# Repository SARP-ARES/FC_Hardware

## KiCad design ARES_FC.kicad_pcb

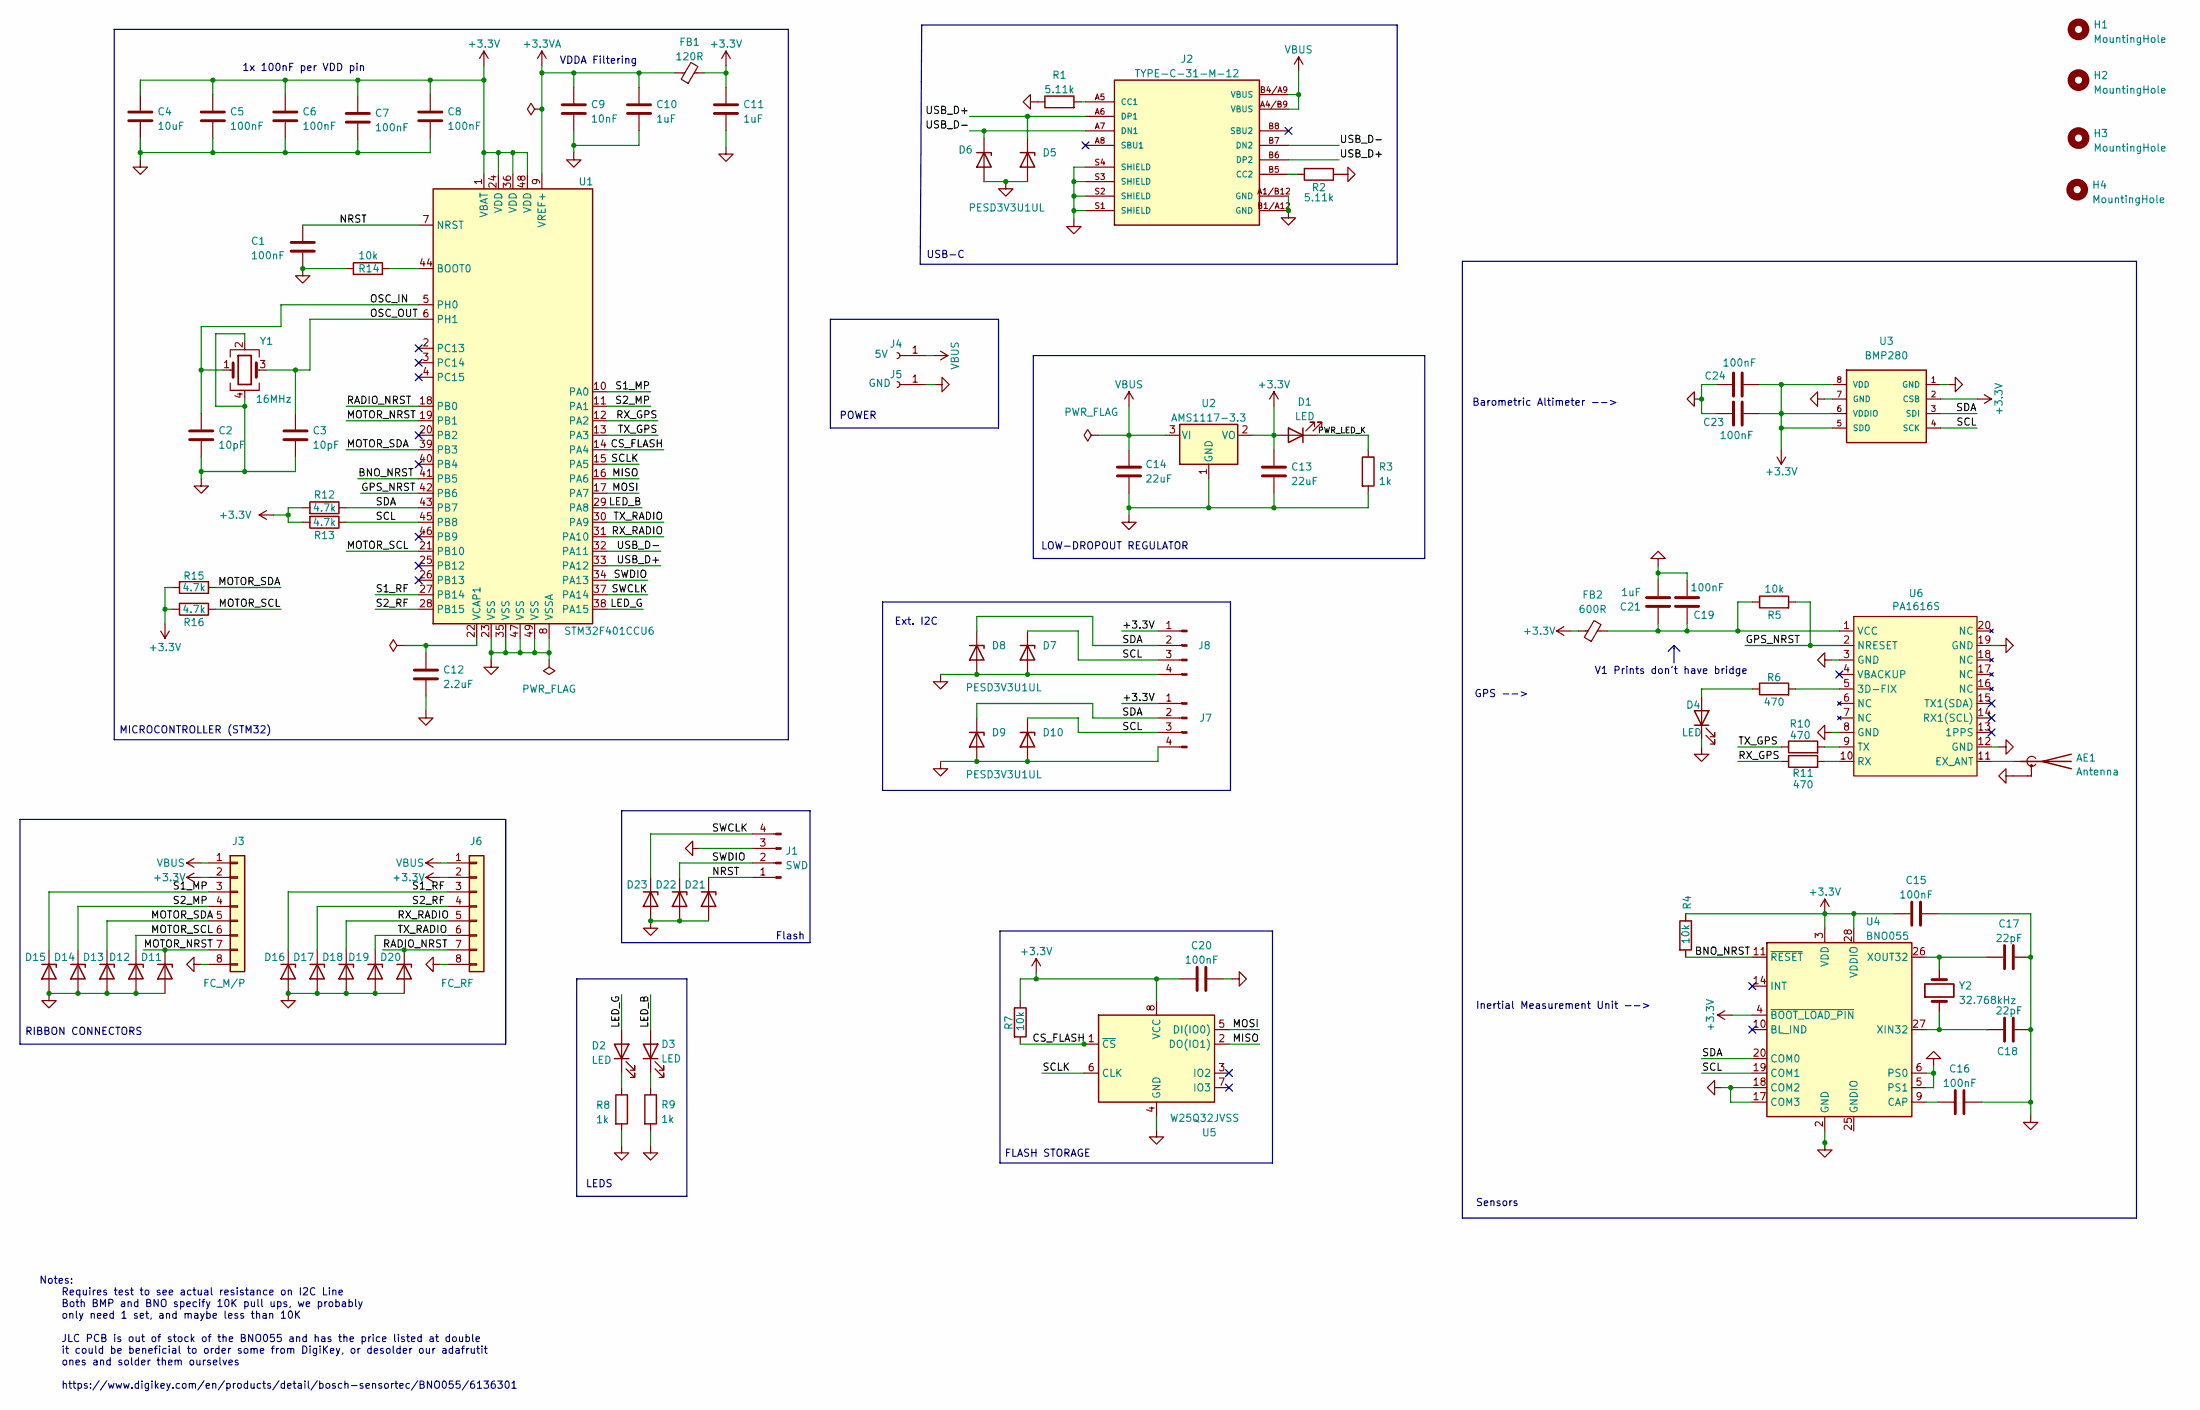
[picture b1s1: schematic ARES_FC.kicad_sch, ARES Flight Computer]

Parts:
AE1: Antenna; U.FL_Molex_MCRF_73412-0110_Vertical; LCSC Part C5137195
C1, C5, C6, C7, C8, C15, C16, C19, C20, C23, C24: 100nF; C_0402_1005Metric; LCSC Part C307331
C2, C3: 10pF; C_0402_1005Metric; LCSC Part C32949
C4: 10uF; C_0603_1608Metric; LCSC Part C19702
C9: 10nF; C_0402_1005Metric; LCSC Part C15195
C10, C11, C21: 1uF; C_0402_1005Metric; LCSC Part C52923
C12: 2.2uF; C_0402_1005Metric; LCSC Part C12530
C13, C14: 22uF; C_0805_2012Metric; LCSC Part C5674
C17, C18: 22pF; C_0402_1005Metric; LCSC Part C466226
D1, D2: LED; LED_0603_1608Metric; LCSC Part C12624
D3: LED; LED_0603_1608Metric; LCSC Part C2288
D4: LED; LED_0603_1608Metric; LCSC Part C2290
D5, D6, D7, D8, D9, D10, D11, D12, D13, D14, D15, D16, D17, D18, D19, D20, D21, D22, D23: PESD3V3U1UL; D_SOD-882
FB1: 120R; L_0603_1608Metric; LCSC Part C85831
FB2: 600R; L_0603_1608Metric; LCSC Part C88976
H1, H2, H3, H4: MountingHole; MountingHole_2.2mm_M2
J1: SWD; PinHeader_1x04_P2.54mm_Vertical; LCSC Part C3025061
J2: TYPE-C-31-M-12; HRO_TYPE-C-31-M-12; PARTREV 2020.12.08; LCSC Part C165948
J3: FC_M/P; Molex_200528-0080_1x08-1MP_P1.00mm_Horizontal; LCSC Part C132510
J4: 5V; TestPoint_THTPad_2.5x2.5mm_Drill1.2mm
J5: GND; TestPoint_THTPad_2.5x2.5mm_Drill1.2mm
J6: FC_RF; Molex_200528-0080_1x08-1MP_P1.00mm_Horizontal; LCSC Part C132510
J7, J8: Conn_01x04_Pin; JST_SH_BM04B-SRSS-TB_1x04-1MP_P1.00mm_Vertical; LCSC Part C160390
R1, R2: 5.11k; R_0402_1005Metric; LCSC Part C25906
R3, R8, R9: 1k; R_0402_1005Metric; LCSC Part C11702
R4, R5, R7, R14: 10k; R_0402_1005Metric; LCSC Part C60490
R6, R10, R11: 470; R_0402_1005Metric; LCSC Part 0402WGJ0471TCE
R12, R13, R15, R16: 4.7k; R_0402_1005Metric; LCSC Part C25900
U1: STM32F401CCU6; QFN-48-1EP_7x7mm_P0.5mm_EP5.6x5.6mm; LCSC Part C79861
U2: AMS1117-3.3; SOT-223-3_TabPin2; LCSC Part C6186
U3: BMP280; XDCR_BMP280; PART_REV 1.19; LCSC Part C83291
U4: BNO055; LGA-28_5.2x3.8mm_P0.5mm; LCSC Part C93216
U5: W25Q32JVSS; SOIC-8_5.23x5.23mm_P1.27mm; LCSC Part C82344
U6: PA1616S; XCVR_CD-PA1616D; LCSC Part C9900146965
Y1: 16MHz; Crystal_SMD_3225-4Pin_3.2x2.5mm; LCSC Part C13738
Y2: 32.768kHz; Crystal_SMD_3215-2Pin_3.2x1.5mm; LCSC Part C32346

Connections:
+3.3V: C4.1, C5.1, C6.1, C7.1, C8.1, C11.1, C13.1, C15.1, C20.1, C23.2, C24.2, D1.2 (A), FB1.2, FB2.1, J3.2, J6.2, J7.1, J8.1, R4.1, R7.1, R12.2, R13.2, R15.2, R16.2, U1.1 (VBAT), U1.24 (VDD), U1.36 (VDD), U1.48 (VDD), U2.2 (VO), U3.2 (CSB), U3.5 (SDO), U3.6 (VDDIO), U3.8 (VDD), U4.3 (VDD), U4.4 (~BOOT_LOAD_PIN), U4.28 (VDDIO), U5.8 (VCC)
+3.3VA: C9.1, C10.1, FB1.1, U1.9 (VREF+)
/BNO_NRST: R4.2, U1.41 (PB5), U4.11 (~RESET)
/CS_FLASH: R7.2, U1.14 (PA4), U5.1 (~CS)
/GPS_NRST: R5.2, U1.42 (PB6), U6.2 (NRESET)
/LED_B: D3.2 (A), U1.29 (PA8)
/LED_G: D2.2 (A), U1.38 (PA15)
/MISO: U1.16 (PA6), U5.2 (DO(IO1))
/MOSI: U1.17 (PA7), U5.5 (DI(IO0))
/MOTOR_NRST: D11.1 (K), J3.7, U1.19 (PB1)
/MOTOR_SCL: D12.1 (K), J3.6, R16.1, U1.21 (PB10)
/MOTOR_SDA: D13.1 (K), J3.5, R15.1, U1.39 (PB3)
/NRST: C1.2, D21.1 (K), J1.1, U1.7 (NRST)
/OSC_IN: C2.1, U1.5 (PH0), Y1.1
/OSC_OUT: C3.1, U1.6 (PH1), Y1.3
/PWR_LED_K: D1.1 (K), R3.1
/RADIO_NRST: D20.1 (K), J6.7, U1.18 (PB0)
/RX_GPS: R11.1, U1.12 (PA2)
/RX_RADIO: D18.1 (K), J6.5, U1.31 (PA10)
/S1_MP: D15.1 (K), J3.3, U1.10 (PA0)
/S1_RF: D16.1 (K), J6.3, U1.27 (PB14)
/S2_MP: D14.1 (K), J3.4, U1.11 (PA1)
/S2_RF: D17.1 (K), J6.4, U1.28 (PB15)
/SCL: D7.1 (K), D10.1 (K), J7.3, J8.3, R13.1, U1.45 (PB8), U3.4 (SCK), U4.19 (COM1)
/SCLK: U1.15 (PA5), U5.6 (CLK)
/SDA: D8.1 (K), D9.1 (K), J7.2, J8.2, R12.1, U1.43 (PB7), U3.3 (SDI), U4.20 (COM0)
/SWCLK: D23.1 (K), J1.4, U1.37 (PA14)
/SWDIO: D22.1 (K), J1.2, U1.34 (PA13)
/TX_GPS: R10.1, U1.13 (PA3)
/TX_RADIO: D19.1 (K), J6.6, U1.30 (PA9)
/USB_D+: D5.1 (K), J2.A6 (DP1), J2.B6 (DP2), U1.33 (PA12)
/USB_D-: D6.1 (K), J2.A7 (DN1), J2.B7 (DN2), U1.32 (PA11)
GND: AE1.2 (Shield), C1.1, C2.2, C3.2, C4.2, C5.2, C6.2, C7.2, C8.2, C9.2, C10.2, C11.2, C12.2, C13.2, C14.2, C15.2, C16.2, C17.2, C18.2, C19.2, C20.2, C21.2, C23.1, C24.1, D4.1 (K), D5.2 (A), D6.2 (A), D7.2 (A), D8.2 (A), D9.2 (A), D10.2 (A), D11.2 (A), D12.2 (A), D13.2 (A), D14.2 (A), D15.2 (A), D16.2 (A), D17.2 (A), D18.2 (A), D19.2 (A), D20.2 (A), D21.2 (A), D22.2 (A), D23.2 (A), J1.3, J2.A1/B12 (GND), J2.B1/A12 (GND), J2.S1 (SHIELD), J2.S2 (SHIELD), J2.S3 (SHIELD), J2.S4 (SHIELD), J3.8, J5.1, J6.8, J7.4, J8.4, R1.1, R2.1, R3.2, R8.2, R9.2, R14.1, U1.8 (VSSA), U1.23 (VSS), U1.35 (VSS), U1.47 (VSS), U1.49 (VSS), U2.1 (GND), U3.1 (GND), U3.7 (GND), U4.2 (GND), U4.5 (PS1), U4.6 (PS0), U4.17 (COM3), U4.18 (COM2), U5.4 (GND), U6.3 (GND), U6.8 (GND), U6.12 (GND), U6.19 (GND), Y1.2, Y1.4
unnamed: AE1.1 (A), U6.11 (EX_ANT)
unnamed: D2.1 (K), R8.1
unnamed: D3.1 (K), R9.1
unnamed: D4.2 (A), R6.1
unnamed: J2.A5 (CC1), R1.2
unnamed: J2.B5 (CC2), R2.2
unnamed: R14.2, U1.44 (BOOT0)
unnamed: C12.1, U1.22 (VCAP1)
unnamed: C16.1, U4.9 (CAP)
unnamed: U4.15 (GNDIO), U4.16 (GNDIO), U4.25 (GNDIO)
unnamed: C18.1, U4.27 (XIN32), Y2.1
unnamed: C17.1, U4.26 (XOUT32), Y2.2
unnamed: R6.2, U6.5 (3D-FIX)
unnamed: R11.2, U6.10 (RX)
unnamed: R10.2, U6.9 (TX)
unnamed: C19.1, C21.1, FB2.2, R5.1, U6.1 (VCC)
VBUS: C14.1, J2.A4/B9 (VBUS), J2.B4/A9 (VBUS), J3.1, J4.1, J6.1, U2.3 (VI)

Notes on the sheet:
VDDA Filtering
Flash
Barometric Altimeter -->
LOW-DROPOUT REGULATOR
FLASH STORAGE
GPS -->
V1 Prints don't have bridge
1x 100nF per VDD pin
LEDS
Notes: Requires test to see actual resistance on I2C Line Both BMP and BNO specify 10K pull ups, we probably only need 1 set, and maybe less than 10K JLC PCB is out of stock of the BNO055 and has the price listed at double it could be beneficial to order some from DigiKey, or desolder our adafrutit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
USB-C
RIBBON CONNECTORS
Inertial Measurement Unit -->
Ext. I2C
MICROCONTROLLER (STM32)
POWER
Sensors

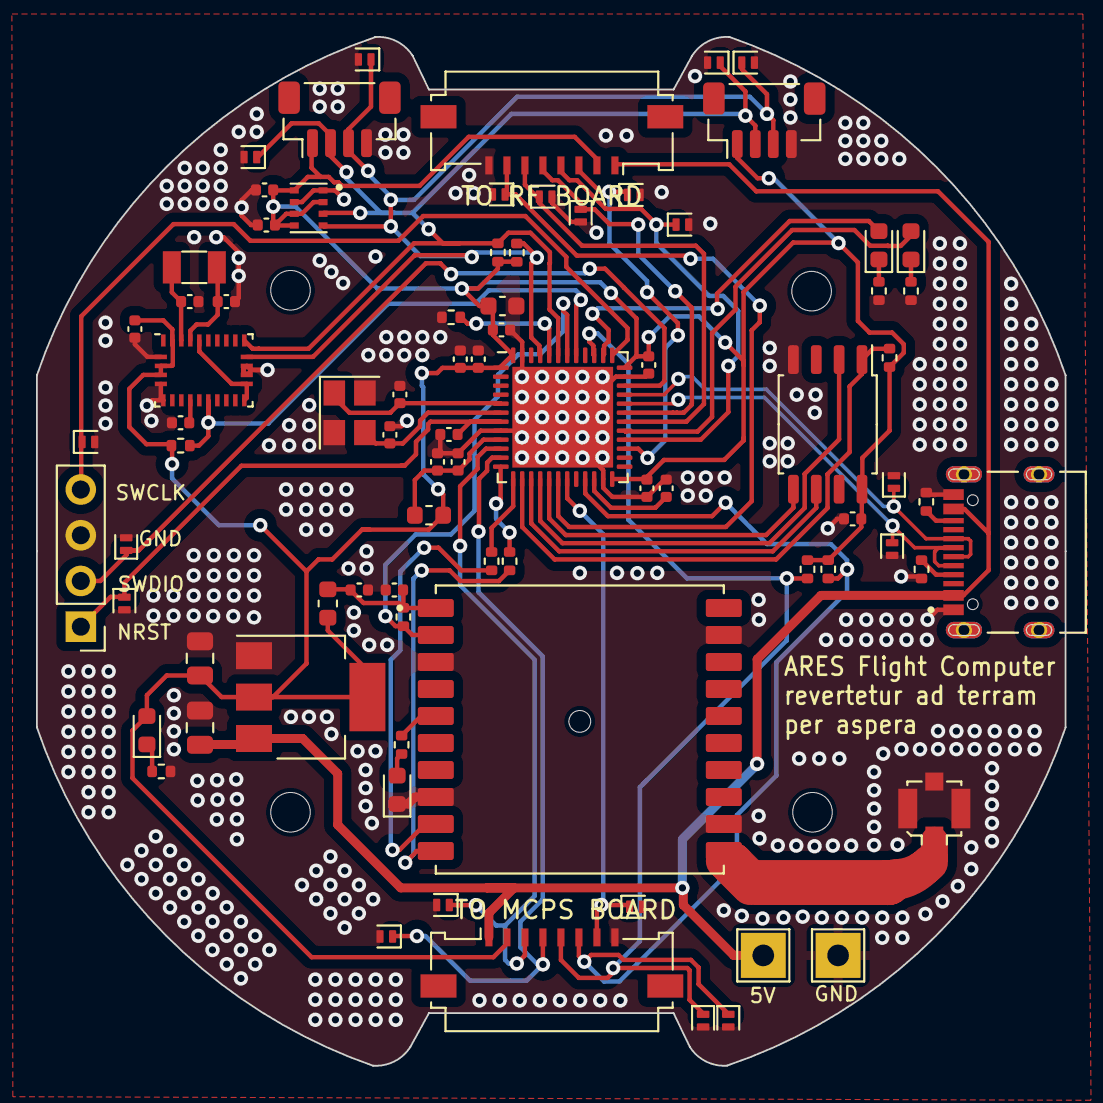
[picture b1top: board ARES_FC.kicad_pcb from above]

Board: 2 copper layers, 57.2 x 57.2 mm, 85 parts (0 on the bottom side), 50 nets.

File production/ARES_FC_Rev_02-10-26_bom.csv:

Designator,Footprint,Quantity,Value,LCSC Part #
AE1,U.FL_Molex_MCRF_73412-0110_Vertical,1,Antenna,C5137195
"C1, C15, C16, C19, C20, C23, C24, C5, C6, C7, C8",0402,11,100nF,C307331
"C10, C11, C21",0402,3,1uF,C52923
C12,0402,1,2.2uF,C12530
"C13, C14",0805,2,22uF,C5674
"C17, C18",0402,2,22pF,C466226
"C2, C3",0402,2,10pF,C32949
C4,0603,1,10uF,C19702
C9,0402,1,10nF,C15195
"D1, D2",0603,2,LED,C12624
"D10, D11, D12, D13, D14, D15, D16, D17, D18, D19, D20, D21, D22, D23, D5, D6, D7, D8, D9",D_SOD-882,19,PESD3V3U1UL,
D3,0603,1,LED,C2288
D4,0603,1,LED,C2290
FB1,0603,1,120R,C85831
FB2,0603,1,600R,C88976
"H1, H2, H3, H4",MountingHole_2.2mm_M2,4,MountingHole,
J1,PinHeader_1x04_P2.54mm_Vertical,1,SWD,C3025061
J2,HRO_TYPE-C-31-M-12,1,TYPE-C-31-M-12,C165948
J3,Molex_200528-0080_1x08-1MP_P1.00mm_Horizontal,1,FC_M/P,C132510
J4,TestPoint_THTPad_2.5x2.5mm_Drill1.2mm,1,5V,
J5,TestPoint_THTPad_2.5x2.5mm_Drill1.2mm,1,GND,
J6,Molex_200528-0080_1x08-1MP_P1.00mm_Horizontal,1,FC_RF,C132510
"J7, J8",JST_SH_BM04B-SRSS-TB_1x04-1MP_P1.00mm_Vertical,2,Conn_01x04_Pin,C160390
"R1, R2",0402,2,5.11k,C25906
"R10, R11",0402,2,470,0402WGJ0471TCE 
"R12, R13, R15, R16",0402,4,4.7k,C25900
"R14, R4, R5, R7",0402,4,10k,C60490
"R3, R8, R9",0402,3,1k,C11702
R6,0402,1,470,0402WGJ0471TCE
U1,QFN-48-1EP_7x7mm_P0.5mm_EP5.6x5.6mm,1,STM32F401CCU6,C79861
U2,SOT-223-3_TabPin2,1,AMS1117-3.3,C6186
U3,XDCR_BMP280,1,BMP280,C83291
U4,LGA-28_5.2x3.8mm_P0.5mm,1,BNO055,C93216
U5,SOIC-8_5.23x5.23mm_P1.27mm,1,W25Q32JVSS,C82344
U6,XCVR_CD-PA1616D,1,PA1616S,C9900146965
Y1,Crystal_SMD_3225-4Pin_3.2x2.5mm,1,16MHz,C13738
Y2,Crystal_SMD_3215-2Pin_3.2x1.5mm,1,32.768kHz, C32346

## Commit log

2025-03-06 Moved FC files from old repo
2025-04-18 added gps antenna shielding
2025-10-03 cleaned up schematic a bit
2025-10-09 added gerbers & CPL for ordering
2025-10-09 removed pullup resistor on NRST
    There is already an internal pullup according to the datasheet
2025-10-09 made it prettier
2025-10-10 changed grown plane to solid and cleaned traces
2025-10-11 cleaned up schematic (aesthetic)
2025-10-11 cleaned layout (ground layer -> solid)
2026-01-06 added tvs and boot0
2026-01-06 TVS diodes WIP
2026-01-07 TVS Diodes at connector lines
2026-01-08 Update PCB design and project settings
    Adjusted user text position and removed a segment in the PCB layout. Updated visible layers in the project layout file and added several DRC exclusions in the project settings. Lock files for PCB and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
2026-01-17 changed GPS antenna tracewidth to match impedance and added stitches
2026-01-18 added XT30 to component folder
2026-01-18 rerouted BOOT0 pull-down (was on back side)
2026-02-20 WINTER 2026 ARES FC ORDER
